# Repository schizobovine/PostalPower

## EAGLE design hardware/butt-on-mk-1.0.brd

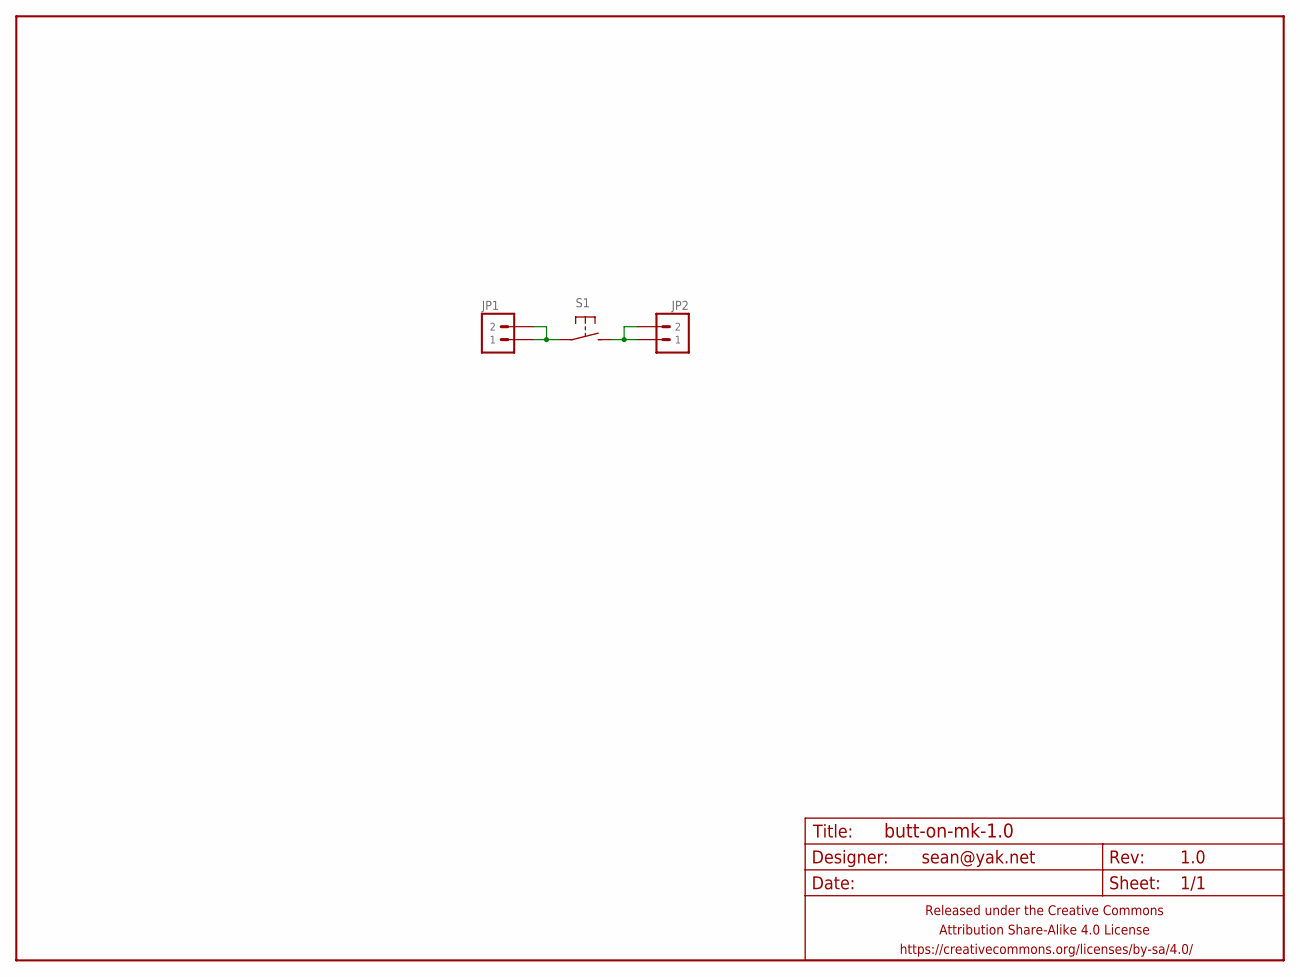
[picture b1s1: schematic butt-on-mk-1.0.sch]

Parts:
FRAME1: FRAME-LETTERNO_PACKAGE; DUMMY
JP1, JP2: M02PTH-CENTERED; 1X02-CENTER
S1: SPST-NO-TACT3MM-PTH-SMALL-PADS; DTS-3-SMALL-PADS

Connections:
unnamed: JP1.1, JP1.2, S1.1
unnamed: JP2.1, JP2.2, S1.2

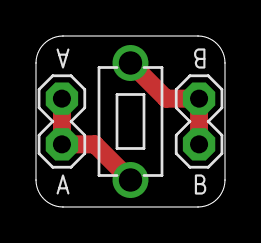
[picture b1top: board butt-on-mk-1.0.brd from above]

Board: 2 copper layers, 10.5 x 9.5 mm, 4 parts (0 on the bottom side), 2 nets.

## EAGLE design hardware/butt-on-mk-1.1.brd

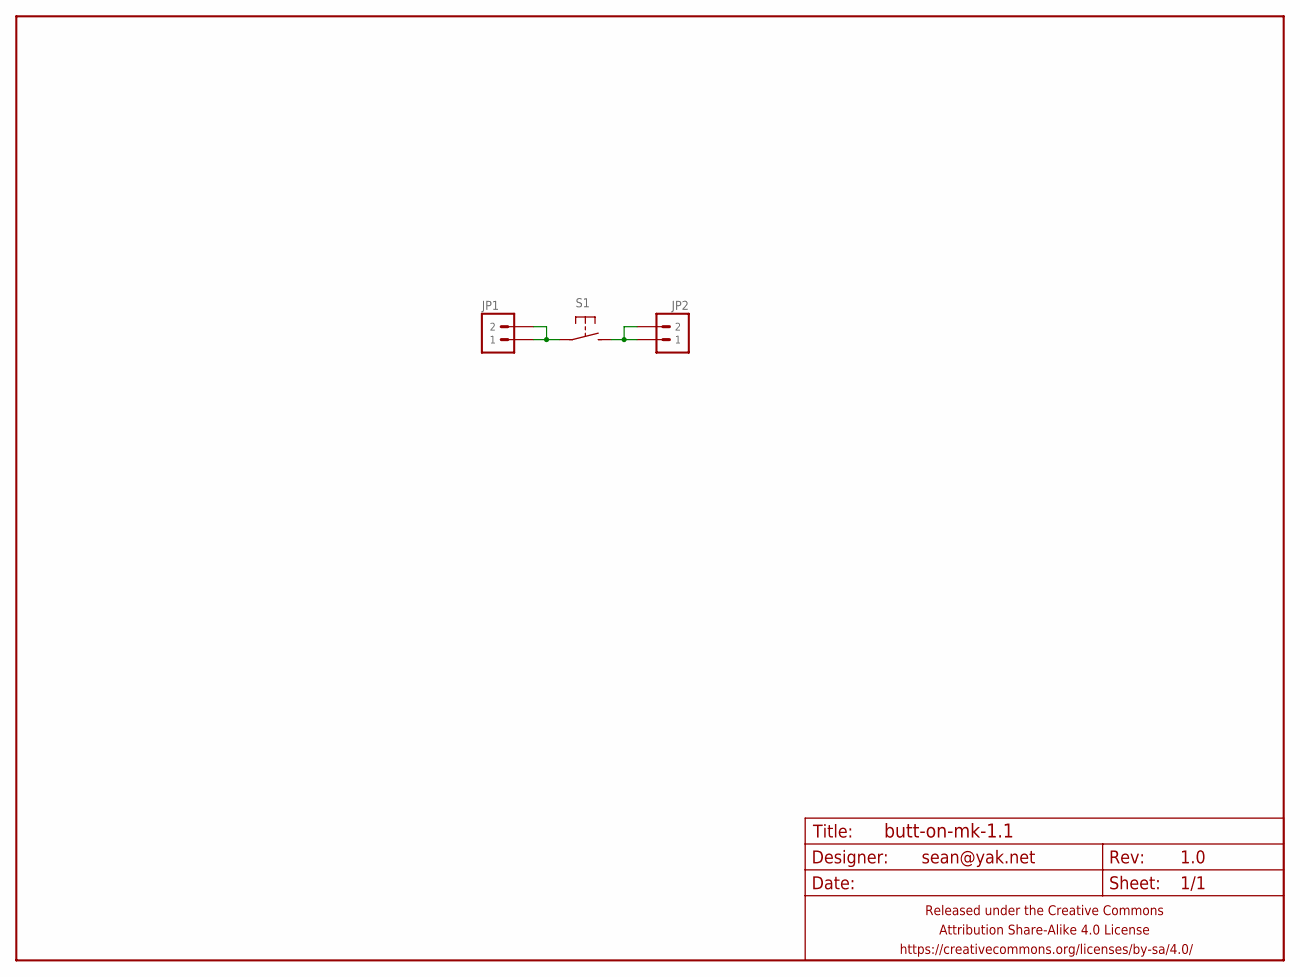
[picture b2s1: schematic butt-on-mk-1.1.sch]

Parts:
FRAME1: FRAME-LETTERNO_PACKAGE; DUMMY
JP1, JP2: M02PTH-CENTERED; 1X02-CENTER
S1: SPST-NO-TACTLESS_SILK; DTS-6-SMALL-PADS-NS

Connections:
unnamed: JP1.1, JP1.2, S1.1, S1.2 (1)
unnamed: JP2.1, JP2.2, S1.3 (2), S1.4 (2)

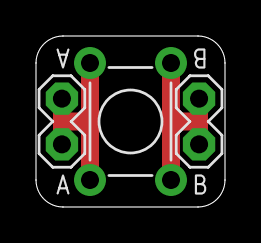
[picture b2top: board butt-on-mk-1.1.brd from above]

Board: 2 copper layers, 10.5 x 9.5 mm, 4 parts (0 on the bottom side), 2 nets.

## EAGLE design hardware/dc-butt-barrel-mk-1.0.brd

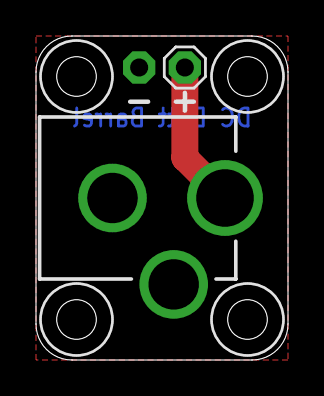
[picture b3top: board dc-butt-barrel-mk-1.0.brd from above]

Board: 2 copper layers, 14.0 x 18.0 mm, 3 parts (0 on the bottom side), 2 nets.

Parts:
FRAME1: FRAME-LETTERNO_PACKAGE; DUMMY
JP1: M02PTH-CENTERED-R+; 1X02-CENTER-R+
PWR1: DCBARRELPTH; DCJACK_2MM_PTH

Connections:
GND: JP1.1, PWR1.BRK, PWR1.GND
VIN: JP1.2, PWR1.PWR

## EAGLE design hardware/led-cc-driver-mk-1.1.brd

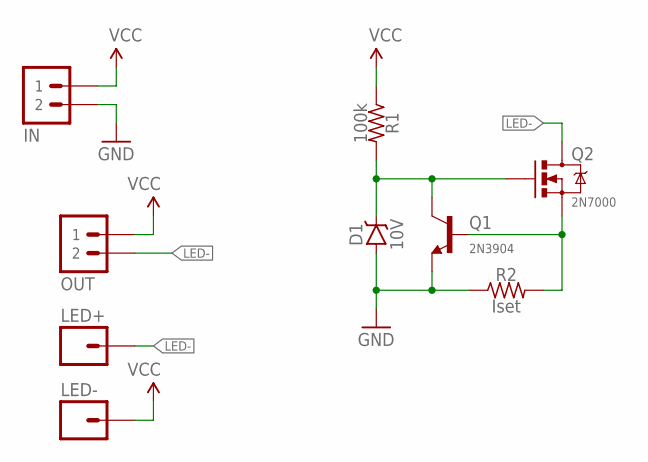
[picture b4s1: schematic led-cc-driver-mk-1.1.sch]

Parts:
D1: 10V; DIODE-ZENNER-7.62MM
IN: M02JST-PTH-RA-SMALLPADS; JST-2-PH-RA-PTH-SMALLPADS
LED+: M01PTH; 1X01
LED-: M01PTH; 1X01
OUT: M02JST-PTH-RA-SMALLPADS; JST-2-PH-RA-PTH-SMALLPADS
Q1: 2N3904; TO-92-AMMO
Q2: 2N7000; TO-92-AMMO
R1: 100k; RESISTOR-AXIAL-PTH-7.62MM
R2: Iset; RESISTOR-AXIAL-PTH-10.16MM

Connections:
BASE: Q1.2 (B), Q2.1 (S), R2.P$2 (2)
GATE: D1.K (C), Q1.3 (C), Q2.2 (G), R1.P$2 (2)
GND: D1.A, IN.2, Q1.1 (E), R2.P$1 (1)
LED-: LED+.1, OUT.2, Q2.3 (D)
VCC: IN.1, LED-.1, OUT.1, R1.P$1 (1)

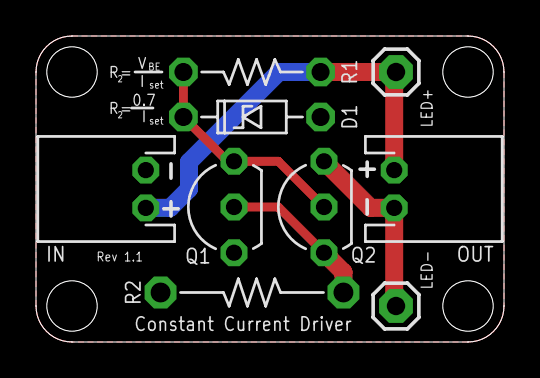
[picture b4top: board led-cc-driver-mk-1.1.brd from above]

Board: 2 copper layers, 26.0 x 17.0 mm, 10 parts (1 on the bottom side), 5 nets.

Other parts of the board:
U$4: CC-BY-SA-4.0-NO-URL

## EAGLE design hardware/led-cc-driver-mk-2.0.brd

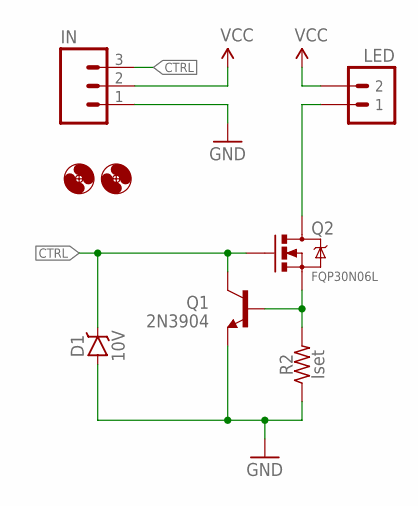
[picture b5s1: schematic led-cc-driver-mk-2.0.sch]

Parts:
D1: 10V; DIODE-ZENNER-7.62MM
H1, H2: HOLE#2; HOLE-#2
IN: M03PTH; 1X03
LED: M02PTH; 1X02
Q1: 2N3904; TO-92-AMMO
Q2: FQP30N06L; TO220-THERMPAD
R2: Iset; RESISTOR-AXIAL-PTH-10.16MM

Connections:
CTRL: D1.K (C), IN.3, Q1.3 (C), Q2.1 (G)
GND: D1.A, IN.1, Q1.1 (E), R2.P$1 (1)
unnamed: Q1.2 (B), Q2.3 (S), R2.P$2 (2)
unnamed: LED.1, Q2.2@1 (D), Q2.2@2 (D)
VCC: IN.2, LED.2

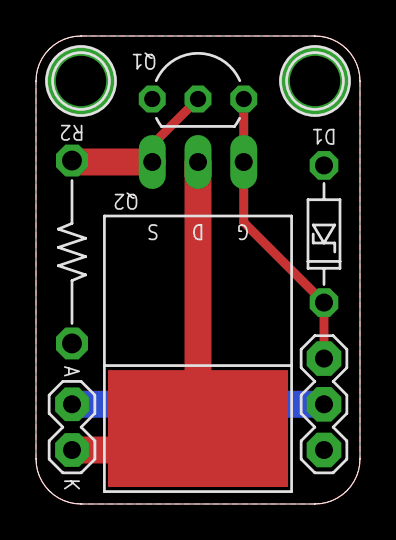
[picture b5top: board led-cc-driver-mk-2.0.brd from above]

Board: 2 copper layers, 18.0 x 26.0 mm, 8 parts (0 on the bottom side), 5 nets.

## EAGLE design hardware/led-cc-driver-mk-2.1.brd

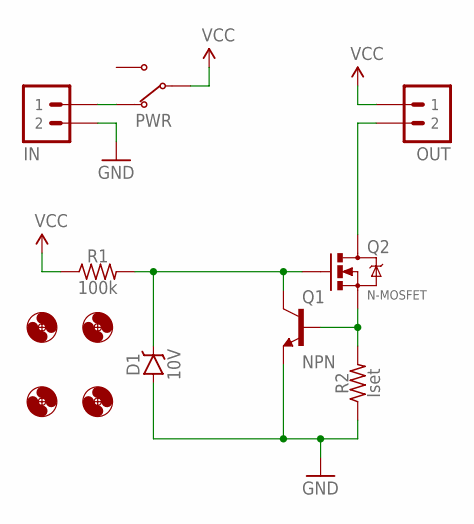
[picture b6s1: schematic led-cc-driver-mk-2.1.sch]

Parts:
D1: 10V; DIODE-ZENNER-7.62MM
H1, H2, H3, H4: HOLE#2; HOLE-#2
IN: M02JST-PTH-RA-SMALLPADS; JST-2-PH-RA-PTH-SMALLPADS
OUT: M02JST-PTH-RA-SMALLPADS; JST-2-PH-RA-PTH-SMALLPADS
PWR: SWITCH-SPDTPTH-VERT-2.54MM; SWITCH-SPDT
Q1: NPN; TO-92-AMMO
Q2: N-MOSFET; TO220-THERMPAD
R1: 100k; RESISTOR-AXIAL-PTH-6.35MM
R2: Iset; RESISTOR-AXIAL-PTH-10.16MM

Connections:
CTRL: D1.K (C), Q1.1 (C), Q2.1 (G), R1.P$2 (2)
GND: D1.A, IN.2, Q1.3 (E), R2.P$1 (1)
unnamed: Q1.2 (B), Q2.3 (S), R2.P$2 (2)
unnamed: IN.1, PWR.1 (NC)
unnamed: OUT.2, Q2.2@1 (D), Q2.2@2 (D)
VCC: OUT.1, PWR.2 (COM), R1.P$1 (1)

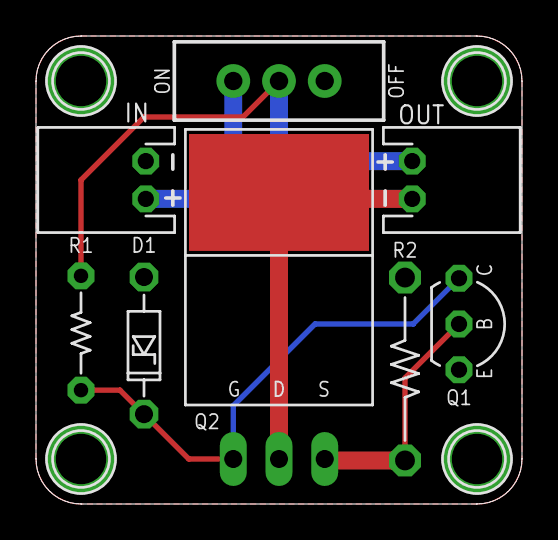
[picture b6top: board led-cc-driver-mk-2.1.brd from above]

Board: 2 copper layers, 27.0 x 26.0 mm, 12 parts (0 on the bottom side), 6 nets.

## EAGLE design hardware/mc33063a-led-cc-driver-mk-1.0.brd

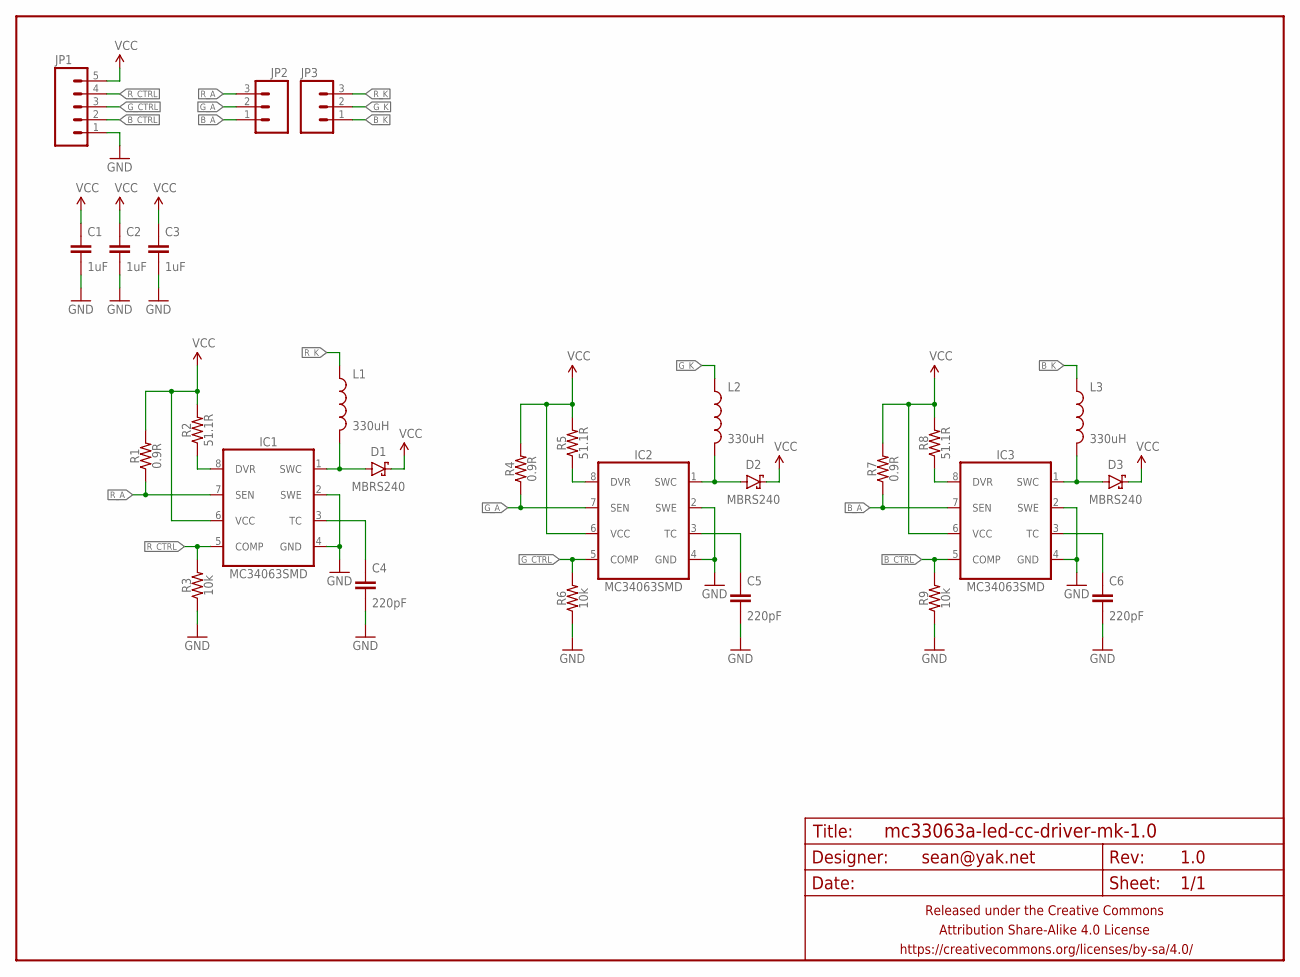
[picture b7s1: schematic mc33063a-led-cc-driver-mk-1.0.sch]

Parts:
C1, C2, C3: 1uF; C0805
C4, C5, C6: 220pF; C0805
D1, D2, D3: MBRS240; SMA-DIODE-SCHOTTKY
FRAME1: FRAME-LETTERNO_PACKAGE; DUMMY
IC1, IC2, IC3: MC34063SMD; SO08
JP1: M05PTH; 1X05
JP2, JP3: M03PTH; 1X03
L1, L2, L3: 330uH; SRN8040
R1, R4, R7: 0.9R; R2010
R2, R5, R8: 51.1R; R1206
R3, R6, R9: 10k; R0805

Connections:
B_A: IC3.7 (SEN), JP2.1, R7.1
B_CTRL: IC3.5 (COMP), JP1.2, R9.2
B_K: JP3.1, L3.1
GND: C1.2, C2.2, C3.2, C4.2, C5.2, C6.2, IC1.2 (SWE), IC1.4 (GND), IC2.2 (SWE), IC2.4 (GND), IC3.2 (SWE), IC3.4 (GND), JP1.1, R3.1, R6.1, R9.1
G_A: IC2.7 (SEN), JP2.2, R4.1
G_CTRL: IC2.5 (COMP), JP1.3, R6.2
G_K: JP3.2, L2.1
unnamed: IC2.8 (DVR), R5.1
unnamed: IC1.8 (DVR), R2.1
unnamed: C5.1, IC2.3 (TC)
unnamed: D2.A, IC2.1 (SWC), L2.2
unnamed: IC3.8 (DVR), R8.1
unnamed: C4.1, IC1.3 (TC)
unnamed: C6.1, IC3.3 (TC)
unnamed: D3.A, IC3.1 (SWC), L3.2
unnamed: D1.A, IC1.1 (SWC), L1.2
R_A: IC1.7 (SEN), JP2.3, R1.1
R_CTRL: IC1.5 (COMP), JP1.4, R3.2
R_K: JP3.3, L1.1
VCC: C1.1, C2.1, C3.1, D1.C, D2.C, D3.C, IC1.6 (VCC), IC2.6 (VCC), IC3.6 (VCC), JP1.5, R1.2, R2.2, R4.2, R5.2, R7.2, R8.2

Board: 2 copper layers, 28 parts (0 on the bottom side), 20 nets, no tracks yet.

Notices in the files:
parts and their libraries:
A_butts: Released under the Creative Commons Attribution Share-Alike 4.0 License
A_butts: https://creativecommons.org/licenses/by-sa/4.0
A_butts: Released under the Creative Commons
